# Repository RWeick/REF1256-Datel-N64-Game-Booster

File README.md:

# REF1256-Datel-N64-Game-Booster
The Kicad files and rom dump for the Datel N64 Game Booster

The Kicad files and rom dump for the Datel N64 Game Booster. The GAL used on this is identical to the one used for the N64 Gameshark and Gameshark Pro. You can make this by transplanting a GAL from a Gameshark.

PCB Thickness: 1.2 mm

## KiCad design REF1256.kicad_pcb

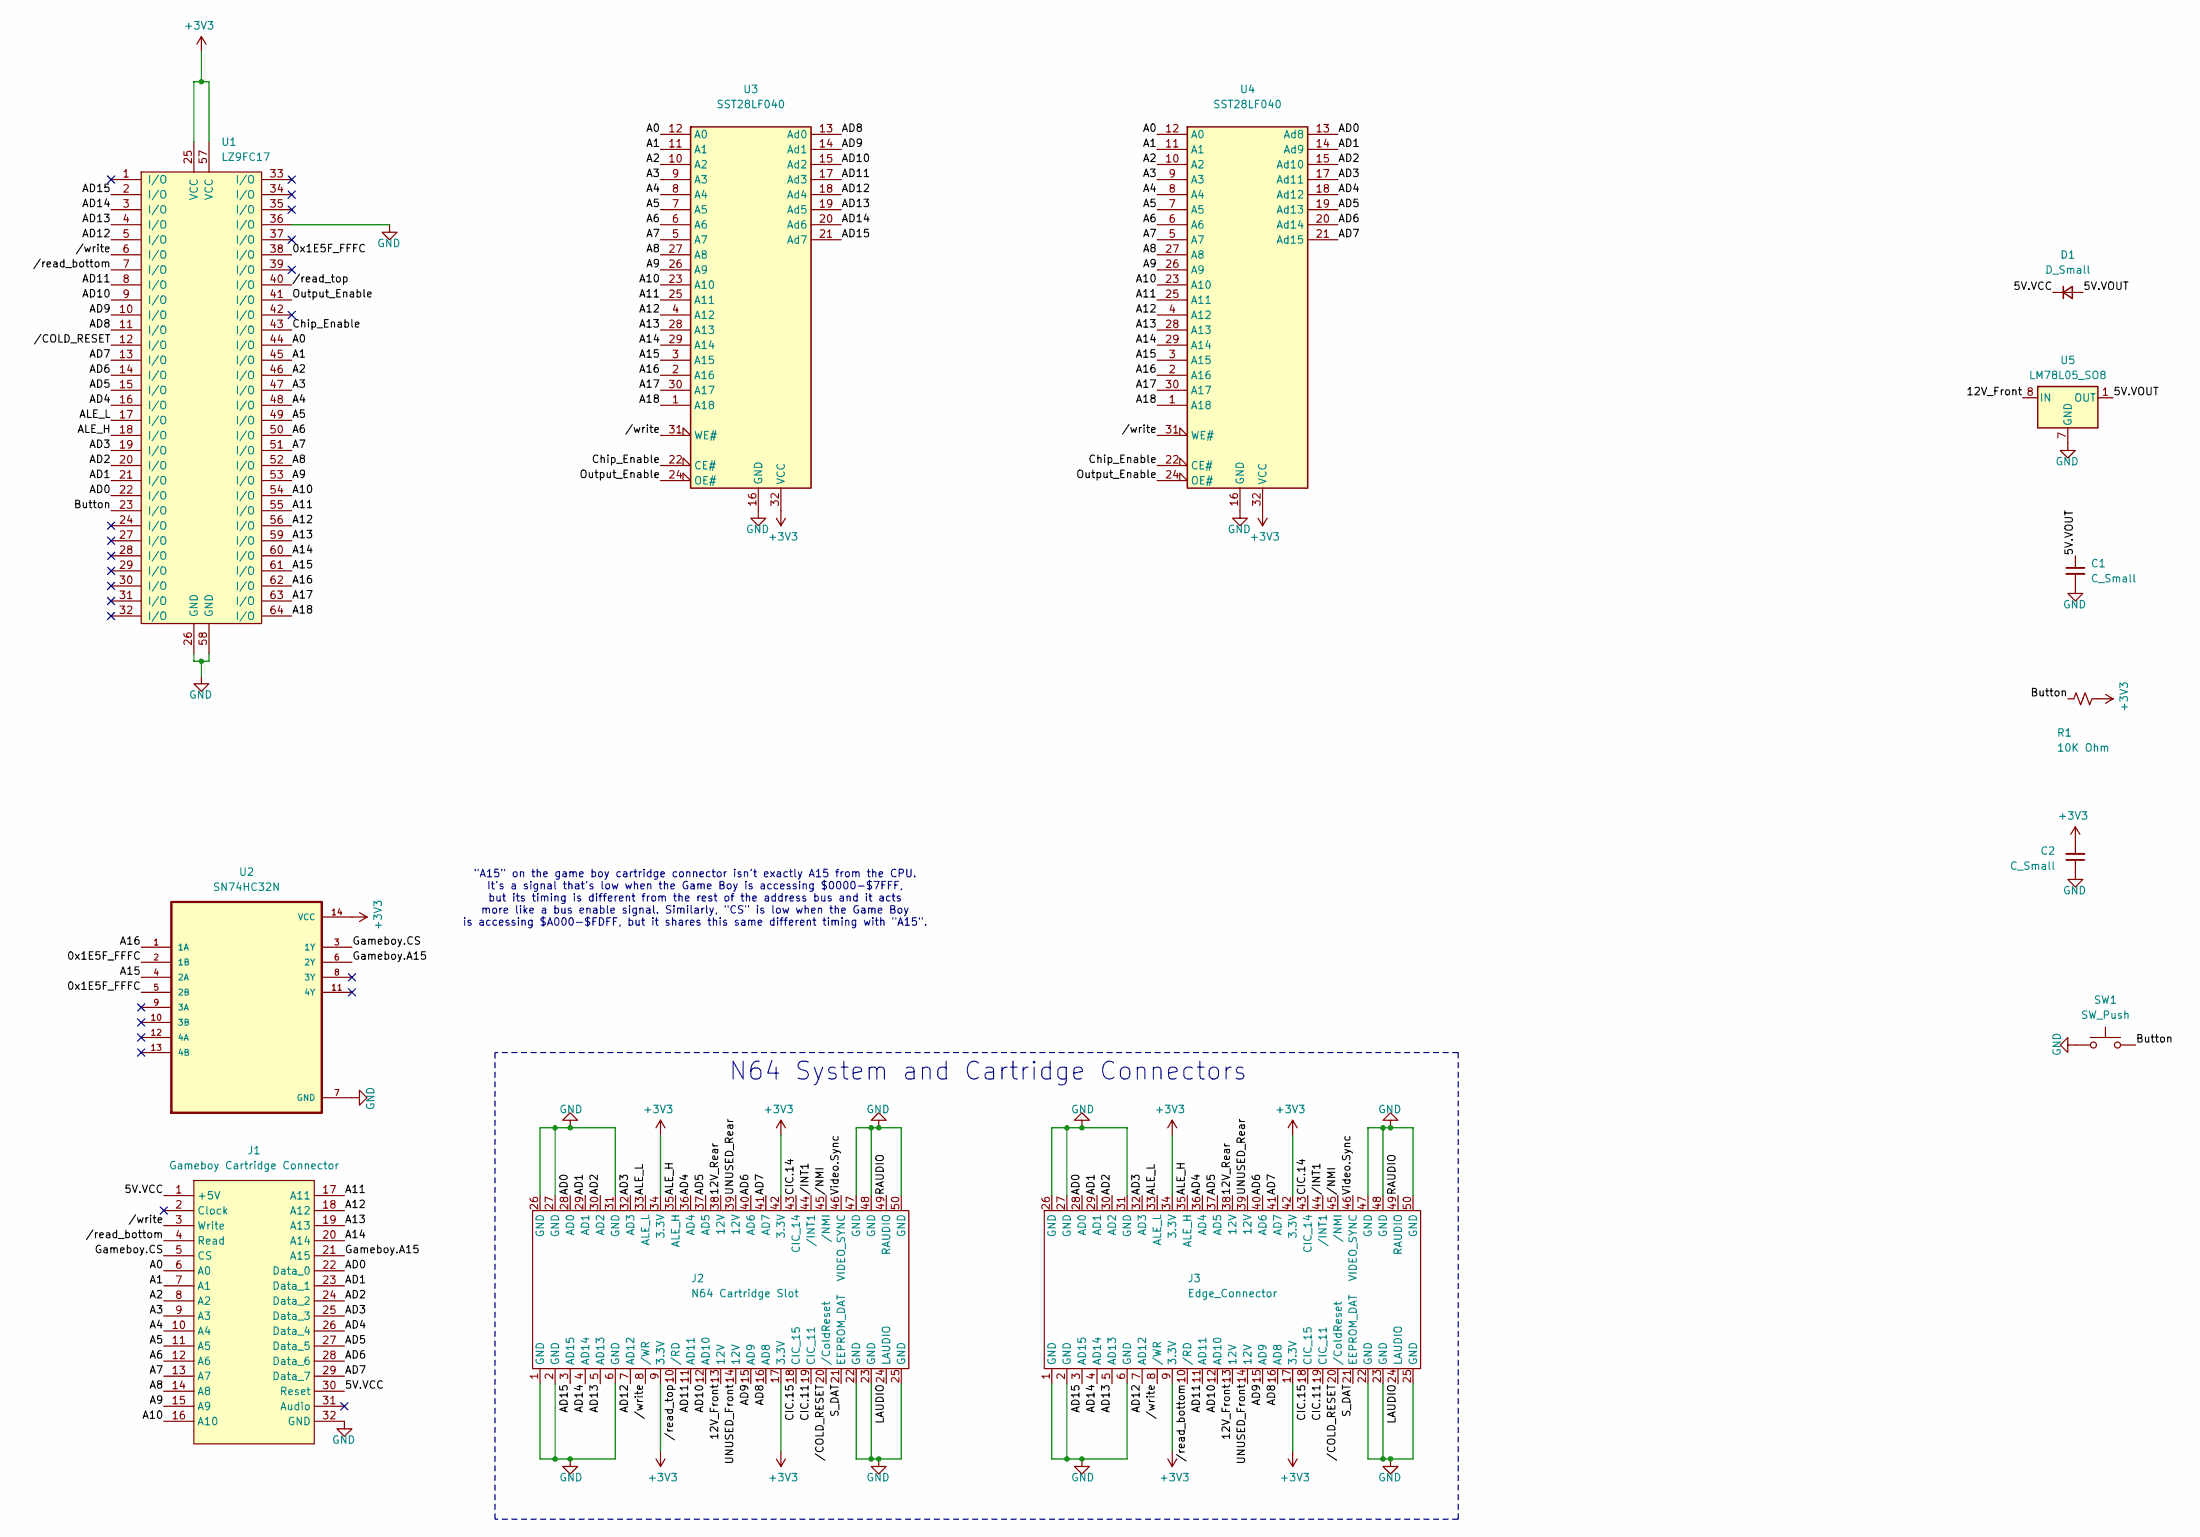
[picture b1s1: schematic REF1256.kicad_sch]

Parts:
C1, C2: C_Small; 100 nF Cap
D1: D_Small; Diode
J1: Gameboy Cartridge Connector; Gameboy Slot
J2: N64 Cartridge Slot; Cartridge Slot
J3: Edge_Connector; Bottom Edge Connector
R1: 10K Ohm; 10k Ohm Resistor
SW1: SW_Push; 6mm Push Button
U1: LZ9FC17; LZ9FC17 GAL
U2: SN74HC32N; 74HC32
U3, U4: SST28LF040; PLCC32
U5: LM78L05_SO8; LM7805

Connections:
+3V3: C2.2, J2.9 (3.3V), J2.17 (3.3V), J2.34 (3.3V), J2.42 (3.3V), J3.9 (3.3V), J3.17 (3.3V), J3.34 (3.3V), J3.42 (3.3V), R1.2, U1.25 (VCC), U1.57 (VCC), U2.14 (VCC), U3.32 (VCC), U4.32 (VCC)
/0x1E5F_FFFC: U1.38 (I/O), U2.2 (1B), U2.5 (2B)
/5V.VCC: D1.1 (K), J1.1 (+5V), J1.30 (Reset)
/5V.VOUT: C1.1, D1.2 (A), U5.1 (OUT)
/12V_Front: J2.13 (12V), J3.13 (12V), U5.8 (IN)
/12V_Rear: J2.38 (12V), J3.38 (12V)
/A0: J1.6 (A0), U1.44 (I/O), U3.12 (A0), U4.12 (A0)
/A1: J1.7 (A1), U1.45 (I/O), U3.11 (A1), U4.11 (A1)
/A2: J1.8 (A2), U1.46 (I/O), U3.10 (A2), U4.10 (A2)
/A3: J1.9 (A3), U1.47 (I/O), U3.9 (A3), U4.9 (A3)
/A4: J1.10 (A4), U1.48 (I/O), U3.8 (A4), U4.8 (A4)
/A5: J1.11 (A5), U1.49 (I/O), U3.7 (A5), U4.7 (A5)
/A6: J1.12 (A6), U1.50 (I/O), U3.6 (A6), U4.6 (A6)
/A7: J1.13 (A7), U1.51 (I/O), U3.5 (A7), U4.5 (A7)
/A8: J1.14 (A8), U1.52 (I/O), U3.27 (A8), U4.27 (A8)
/A9: J1.15 (A9), U1.53 (I/O), U3.26 (A9), U4.26 (A9)
/A10: J1.16 (A10), U1.54 (I/O), U3.23 (A10), U4.23 (A10)
/A11: J1.17 (A11), U1.55 (I/O), U3.25 (A11), U4.25 (A11)
/A12: J1.18 (A12), U1.56 (I/O), U3.4 (A12), U4.4 (A12)
/A13: J1.19 (A13), U1.59 (I/O), U3.28 (A13), U4.28 (A13)
/A14: J1.20 (A14), U1.60 (I/O), U3.29 (A14), U4.29 (A14)
/A15: U1.61 (I/O), U2.4 (2A), U3.3 (A15), U4.3 (A15)
/A16: U1.62 (I/O), U2.1 (1A), U3.2 (A16), U4.2 (A16)
/A17: U1.63 (I/O), U3.30 (A17), U4.30 (A17)
/A18: U1.64 (I/O), U3.1 (A18), U4.1 (A18)
/AD0: J1.22 (Data_0), J2.28 (AD0), J3.28 (AD0), U1.22 (I/O), U4.13 (Ad8)
/AD1: J1.23 (Data_1), J2.29 (AD1), J3.29 (AD1), U1.21 (I/O), U4.14 (Ad9)
/AD2: J1.24 (Data_2), J2.30 (AD2), J3.30 (AD2), U1.20 (I/O), U4.15 (Ad10)
/AD3: J1.25 (Data_3), J2.32 (AD3), J3.32 (AD3), U1.19 (I/O), U4.17 (Ad11)
/AD4: J1.26 (Data_4), J2.36 (AD4), J3.36 (AD4), U1.16 (I/O), U4.18 (Ad12)
/AD5: J1.27 (Data_5), J2.37 (AD5), J3.37 (AD5), U1.15 (I/O), U4.19 (Ad13)
/AD6: J1.28 (Data_6), J2.40 (AD6), J3.40 (AD6), U1.14 (I/O), U4.20 (Ad14)
/AD7: J1.29 (Data_7), J2.41 (AD7), J3.41 (AD7), U1.13 (I/O), U4.21 (Ad15)
/AD8: J2.16 (AD8), J3.16 (AD8), U1.11 (I/O), U3.13 (Ad0)
/AD9: J2.15 (AD9), J3.15 (AD9), U1.10 (I/O), U3.14 (Ad1)
/AD10: J2.12 (AD10), J3.12 (AD10), U1.9 (I/O), U3.15 (Ad2)
/AD11: J2.11 (AD11), J3.11 (AD11), U1.8 (I/O), U3.17 (Ad3)
/AD12: J2.7 (AD12), J3.7 (AD12), U1.5 (I/O), U3.18 (Ad4)
/AD13: J2.5 (AD13), J3.5 (AD13), U1.4 (I/O), U3.19 (Ad5)
/AD14: J2.4 (AD14), J3.4 (AD14), U1.3 (I/O), U3.20 (Ad6)
/AD15: J2.3 (AD15), J3.3 (AD15), U1.2 (I/O), U3.21 (Ad7)
/ALE_H: J2.35 (ALE_H), J3.35 (ALE_H), U1.18 (I/O)
/ALE_L: J2.33 (ALE_L), J3.33 (ALE_L), U1.17 (I/O)
/Button: R1.1, SW1.2, U1.23 (I/O)
/CIC.11: J2.19 (CIC_11), J3.19 (CIC_11)
/CIC.14: J2.43 (CIC_14), J3.43 (CIC_14)
/CIC.15: J2.18 (CIC_15), J3.18 (CIC_15)
/Chip_Enable: U1.43 (I/O), U3.22 (CE#), U4.22 (CE#)
/Gameboy.A15: J1.21 (A15), U2.6 (2Y)
/Gameboy.CS: J1.5 (CS), U2.3 (1Y)
/LAUDIO: J2.24 (LAUDIO), J3.24 (LAUDIO)
/Output_Enable: U1.41 (I/O), U3.24 (OE#), U4.24 (OE#)
/RAUDIO: J2.49 (RAUDIO), J3.49 (RAUDIO)
/S_DAT: J2.21 (EEPROM_DAT), J3.21 (EEPROM_DAT)
/UNUSED_Front: J2.14 (12V), J3.14 (12V)
/UNUSED_Rear: J2.39 (12V), J3.39 (12V)
/Video.Sync: J2.46 (VIDEO_SYNC), J3.46 (VIDEO_SYNC)
//COLD_RESET: J2.20 (/ColdReset), J3.20 (/ColdReset), U1.12 (I/O)
//INT1: J2.44 (/INT1), J3.44 (/INT1)
//NMI: J2.45 (/NMI), J3.45 (/NMI)
//read_bottom: J1.4 (Read), J3.10 (/RD), U1.7 (I/O)
//read_top: J2.10 (/RD), U1.40 (I/O)
//write: J1.3 (Write), J2.8 (/WR), J3.8 (/WR), U1.6 (I/O), U3.31 (WE#), U4.31 (WE#)
GND: C1.2, C2.1, J1.32 (GND), J2.1 (GND), J2.2 (GND), J2.6 (GND), J2.22 (GND), J2.23 (GND), J2.25 (GND), J2.26 (GND), J2.27 (GND), J2.31 (GND), J2.47 (GND), J2.48 (GND), J2.50 (GND), J3.1 (GND), J3.2 (GND), J3.6 (GND), J3.22 (GND), J3.23 (GND), J3.25 (GND), J3.26 (GND), J3.27 (GND), J3.31 (GND), J3.47 (GND), J3.48 (GND), J3.50 (GND), SW1.1, U1.26 (GND), U1.36 (I/O), U1.58 (GND), U2.7 (GND), U3.16 (GND), U4.16 (GND), U5.2 (GND), U5.3 (GND), U5.6 (GND), U5.7 (GND)

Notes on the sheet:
N64 System and Cartridge Connectors
"A15" on the game boy cartridge connector isn't exactly A15 from the CPU. It's a signal that's low when the Game Boy is accessing $0000-$7FFF, but its timing is different from the rest of the address bus and it acts more like a bus enable signal. Similarly, "CS" is low when the Game Boy is accessin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

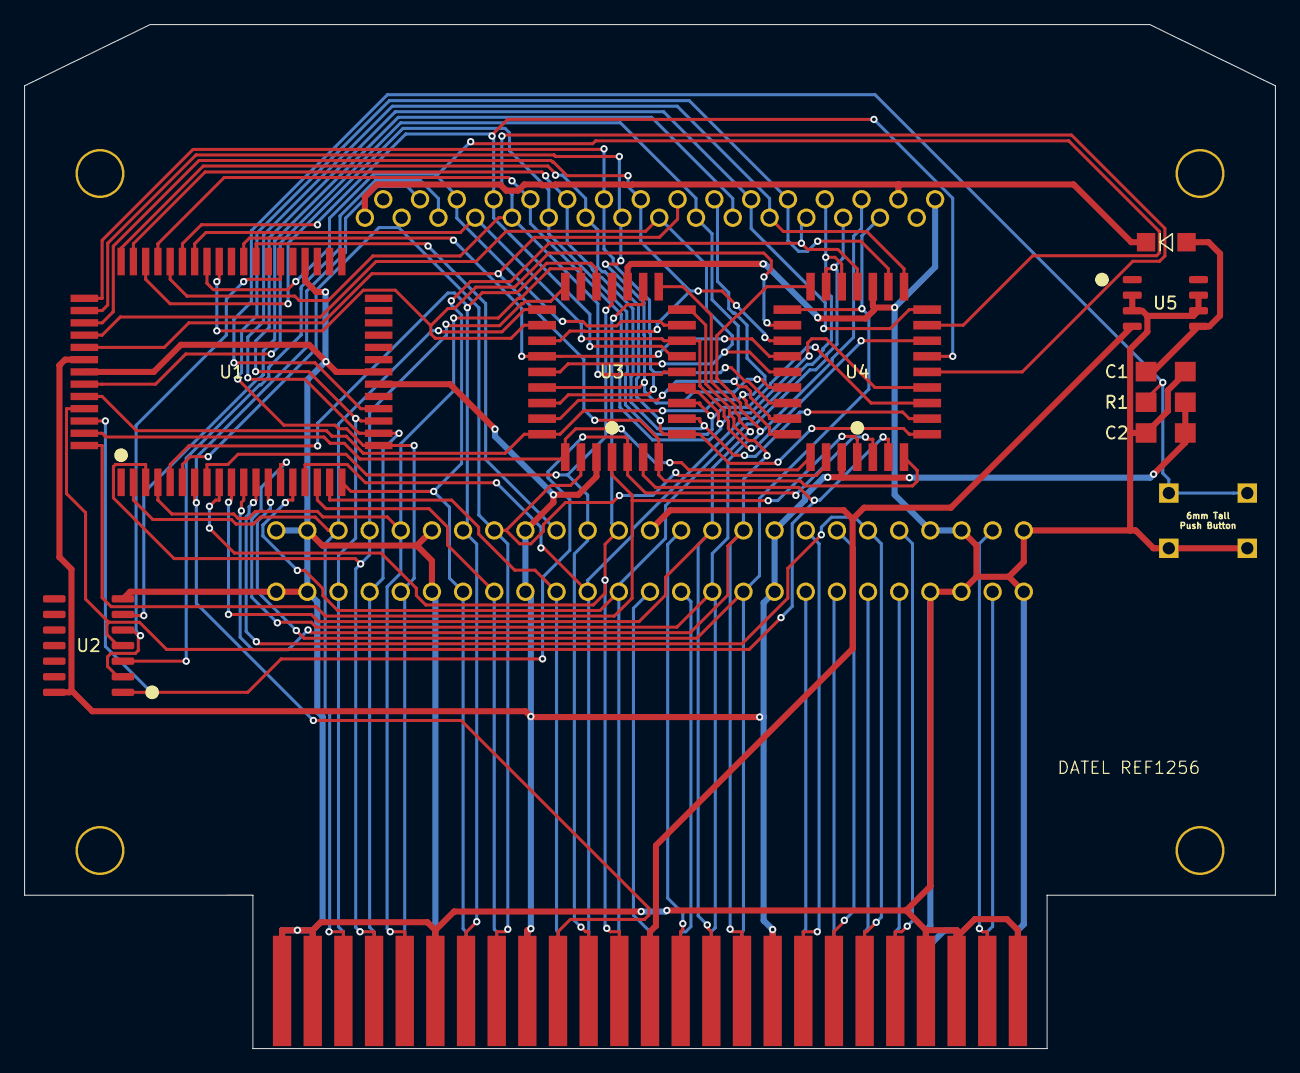
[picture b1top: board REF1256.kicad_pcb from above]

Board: 2 copper layers, 102.0 x 83.5 mm, 14 parts (0 on the bottom side), 64 nets.

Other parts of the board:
Holes: Drill Holes
